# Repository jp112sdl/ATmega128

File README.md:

# ATmega128

```
orig. Fuse:
(E:FF, H:09, L:3F)
```

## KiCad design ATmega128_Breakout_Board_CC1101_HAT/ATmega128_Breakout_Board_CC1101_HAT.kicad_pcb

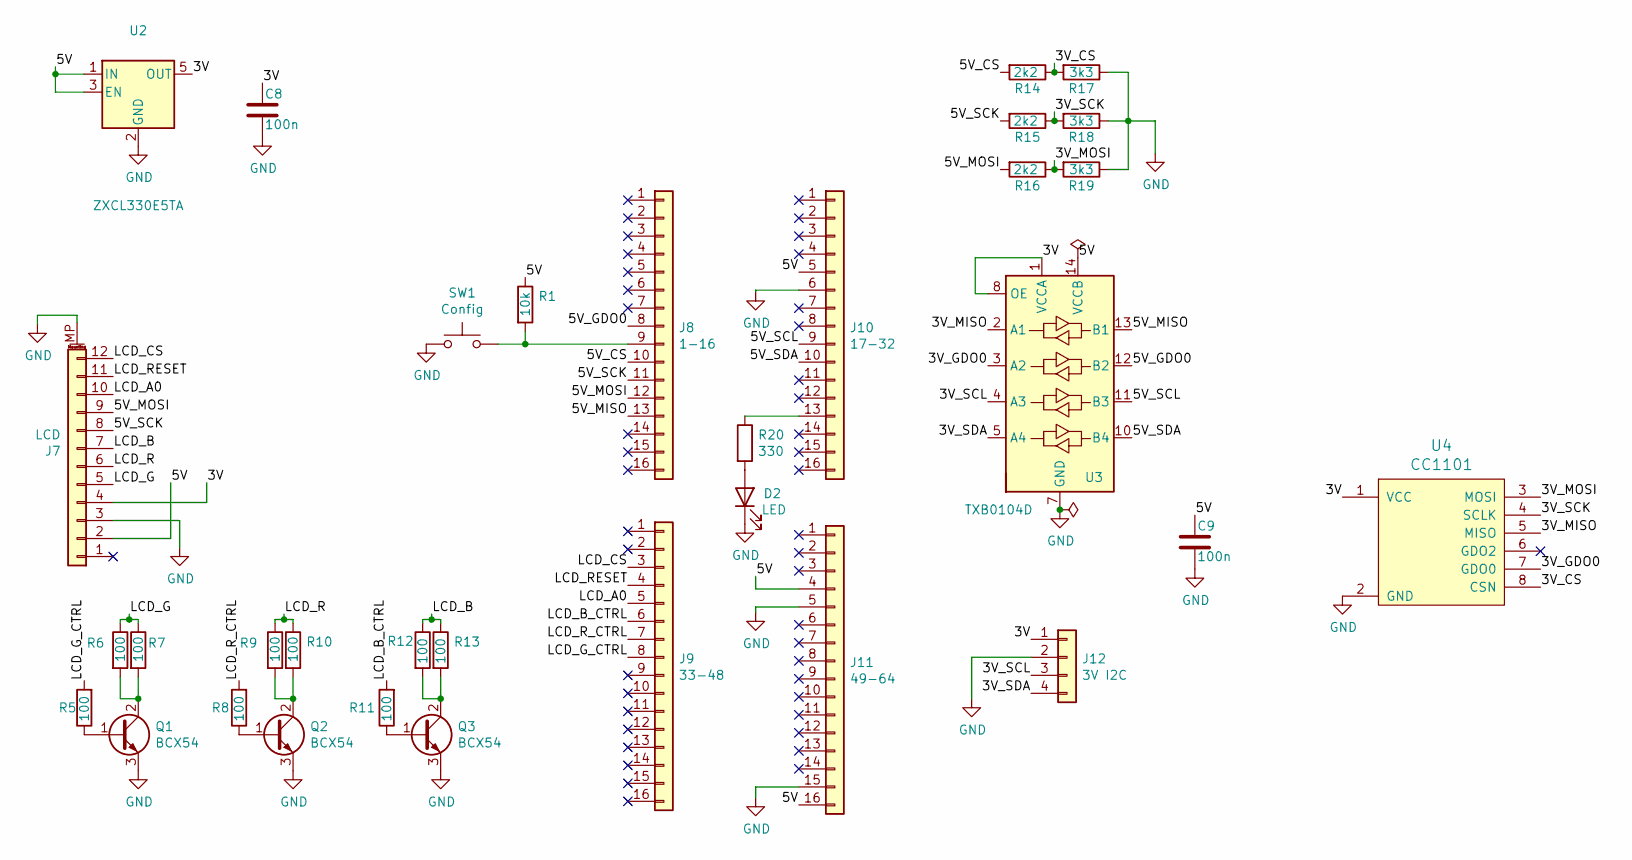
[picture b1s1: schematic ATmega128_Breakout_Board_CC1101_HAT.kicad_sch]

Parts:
C8, C9: 100n; C_0805_2012Metric_Pad1.15x1.40mm_HandSolder
D2: LED; LED_0805_2012Metric_Pad1.15x1.40mm_HandSolder
J7: LCD; TE_1-84953-2_1x12-1MP_P1.0mm_Horizontal
J8: 1-16; PinHeader_1x16_P2.54mm_Vertical
J9: 33-48; PinHeader_1x16_P2.54mm_Vertical
J10: 17-32; PinHeader_1x16_P2.54mm_Vertical
J11: 49-64; PinHeader_1x16_P2.54mm_Vertical
J12: 3V I2C; PinHeader_1x04_P2.54mm_Vertical
Q1, Q2, Q3: BCX54; SOT-89-3
R1: 10k; R_0805_2012Metric_Pad1.15x1.40mm_HandSolder
R5, R6, R7, R8, R9, R10, R11, R12, R13: 100; R_0805_2012Metric_Pad1.15x1.40mm_HandSolder
R14, R15, R16: 2k2; R_0805_2012Metric_Pad1.15x1.40mm_HandSolder
R17, R18, R19: 3k3; R_0805_2012Metric_Pad1.15x1.40mm_HandSolder
R20: 330; R_0805_2012Metric_Pad1.15x1.40mm_HandSolder
SW1: Config; SW_PUSH_6mm_H4.3mm
U2: ZXCL330E5TA; SOT-23-5
U3: TXB0104D; TSSOP-14_4.4x5mm_P0.65mm
U4: CC1101; CC1101_Pads

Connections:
/3V: C8.1, J7.4, J12.1, U2.5 (OUT), U3.1 (VCCA), U3.8 (OE), U4.1 (VCC)
/3V_CS: R14.1, R17.2, U4.8 (CSN)
/3V_GDO0: U3.3 (A2), U4.7 (GDO0)
/3V_MISO: U3.2 (A1), U4.5 (MISO)
/3V_MOSI: R16.1, R19.2, U4.3 (MOSI)
/3V_SCK: R15.1, R18.2, U4.4 (SCLK)
/3V_SCL: J12.3, U3.4 (A3)
/3V_SDA: J12.4, U3.5 (A4)
/5V: C9.1, J7.2, J10.5, J11.4, J11.16, R1.1, U2.1 (IN), U2.3 (EN), U3.14 (VCCB)
/5V_CS: J8.10, R14.2
/5V_GDO0: J8.8, U3.12 (B2)
/5V_MISO: J8.13, U3.13 (B1)
/5V_MOSI: J7.9, J8.12, R16.2
/5V_SCK: J7.8, J8.11, R15.2
/5V_SCL: J10.9, U3.11 (B3)
/5V_SDA: J10.10, U3.10 (B4)
/LCD_A0: J7.10, J9.5
/LCD_B: J7.7, R12.1, R13.1
/LCD_B_CTRL: J9.6, R11.2
/LCD_CS: J7.12, J9.3
/LCD_G: J7.5, R6.1, R7.1
/LCD_G_CTRL: J9.8, R5.2
/LCD_R: J7.6, R9.1, R10.1
/LCD_RESET: J7.11, J9.4
/LCD_R_CTRL: J9.7, R8.2
GND: C8.2, C9.2, D2.1 (K), J7.3, J7.MP (MountPin), J10.6, J11.5, J11.15, J12.2, Q1.3 (E), Q2.3 (E), Q3.3 (E), R17.1, R18.1, R19.1, SW1.1, U2.2 (GND), U3.7 (GND), U4.2 (GND)
unnamed: D2.2 (A), R20.2
unnamed: J8.9, R1.2, SW1.2
unnamed: J10.13, R20.1
unnamed: Q1.1 (B), R5.1
unnamed: Q1.2 (C), R6.2, R7.2
unnamed: Q2.1 (B), R8.1
unnamed: Q2.2 (C), R9.2, R10.2
unnamed: Q3.1 (B), R11.1
unnamed: Q3.2 (C), R12.2, R13.2

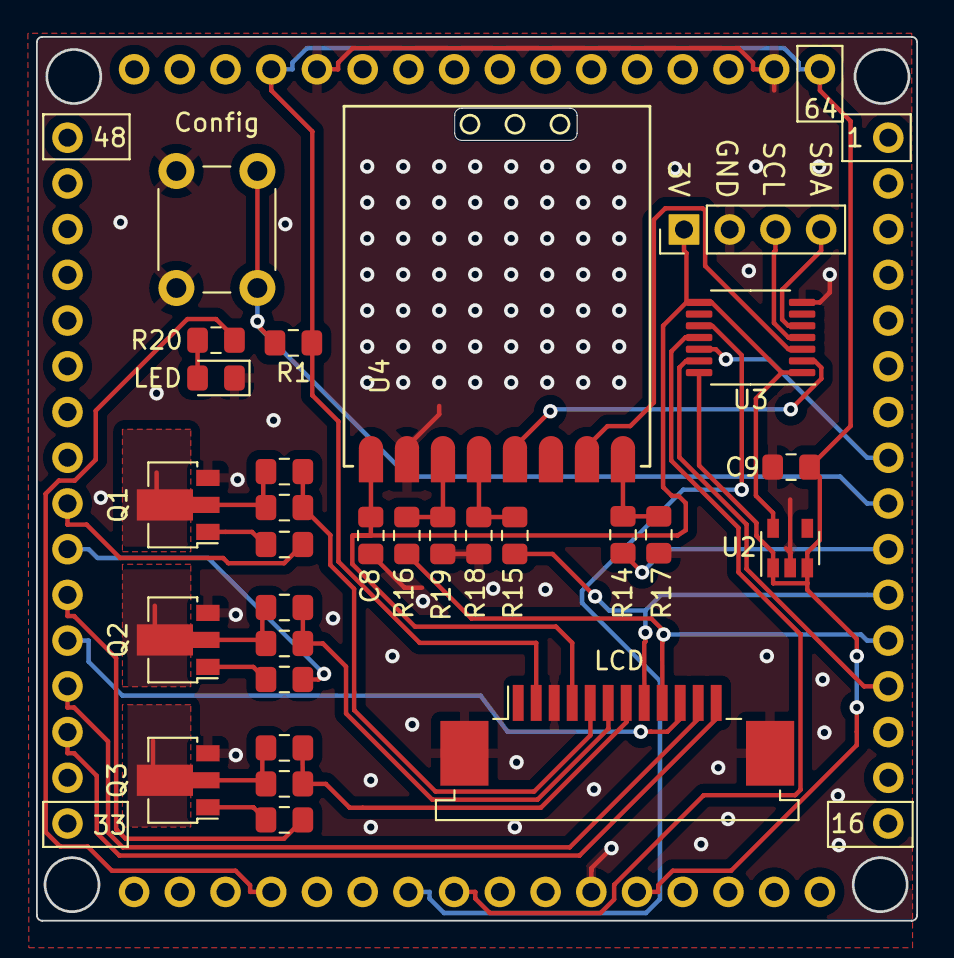
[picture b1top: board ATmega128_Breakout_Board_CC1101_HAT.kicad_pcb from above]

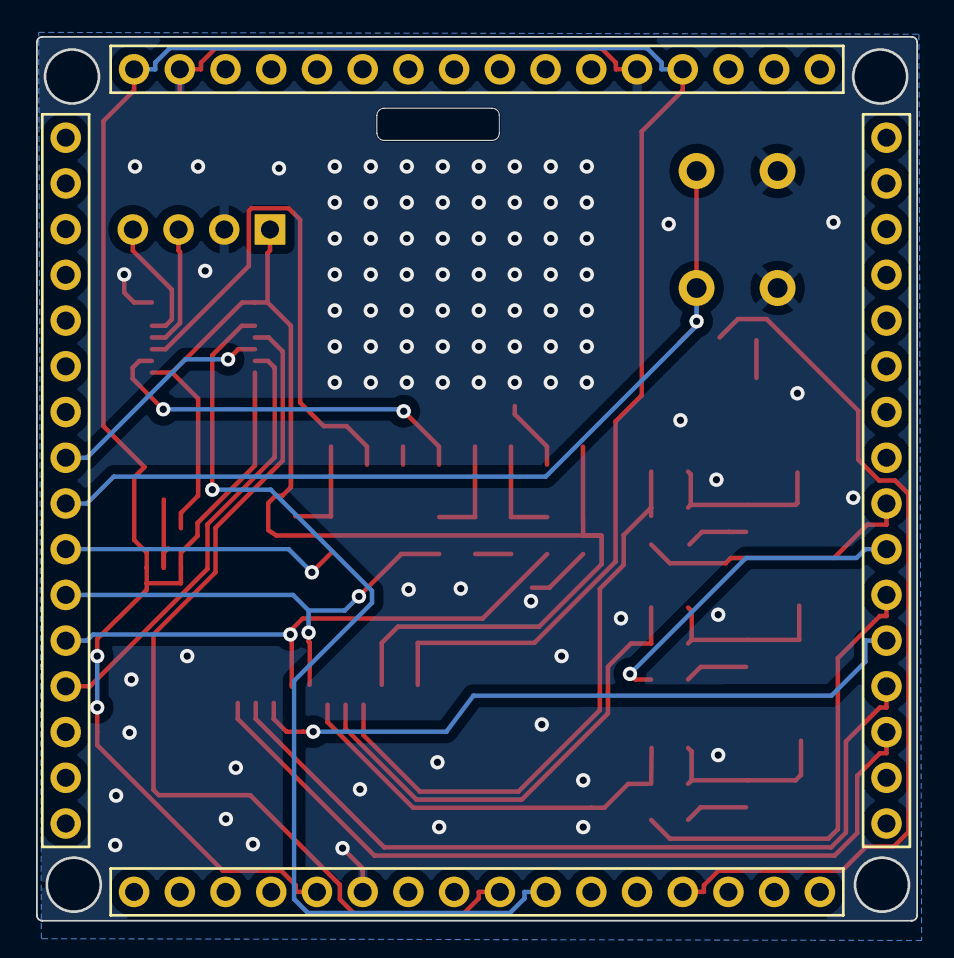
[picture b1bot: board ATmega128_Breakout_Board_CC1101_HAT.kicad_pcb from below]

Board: 2 copper layers, 48.9 x 49.1 mm, 33 parts (4 on the bottom side), 35 nets.

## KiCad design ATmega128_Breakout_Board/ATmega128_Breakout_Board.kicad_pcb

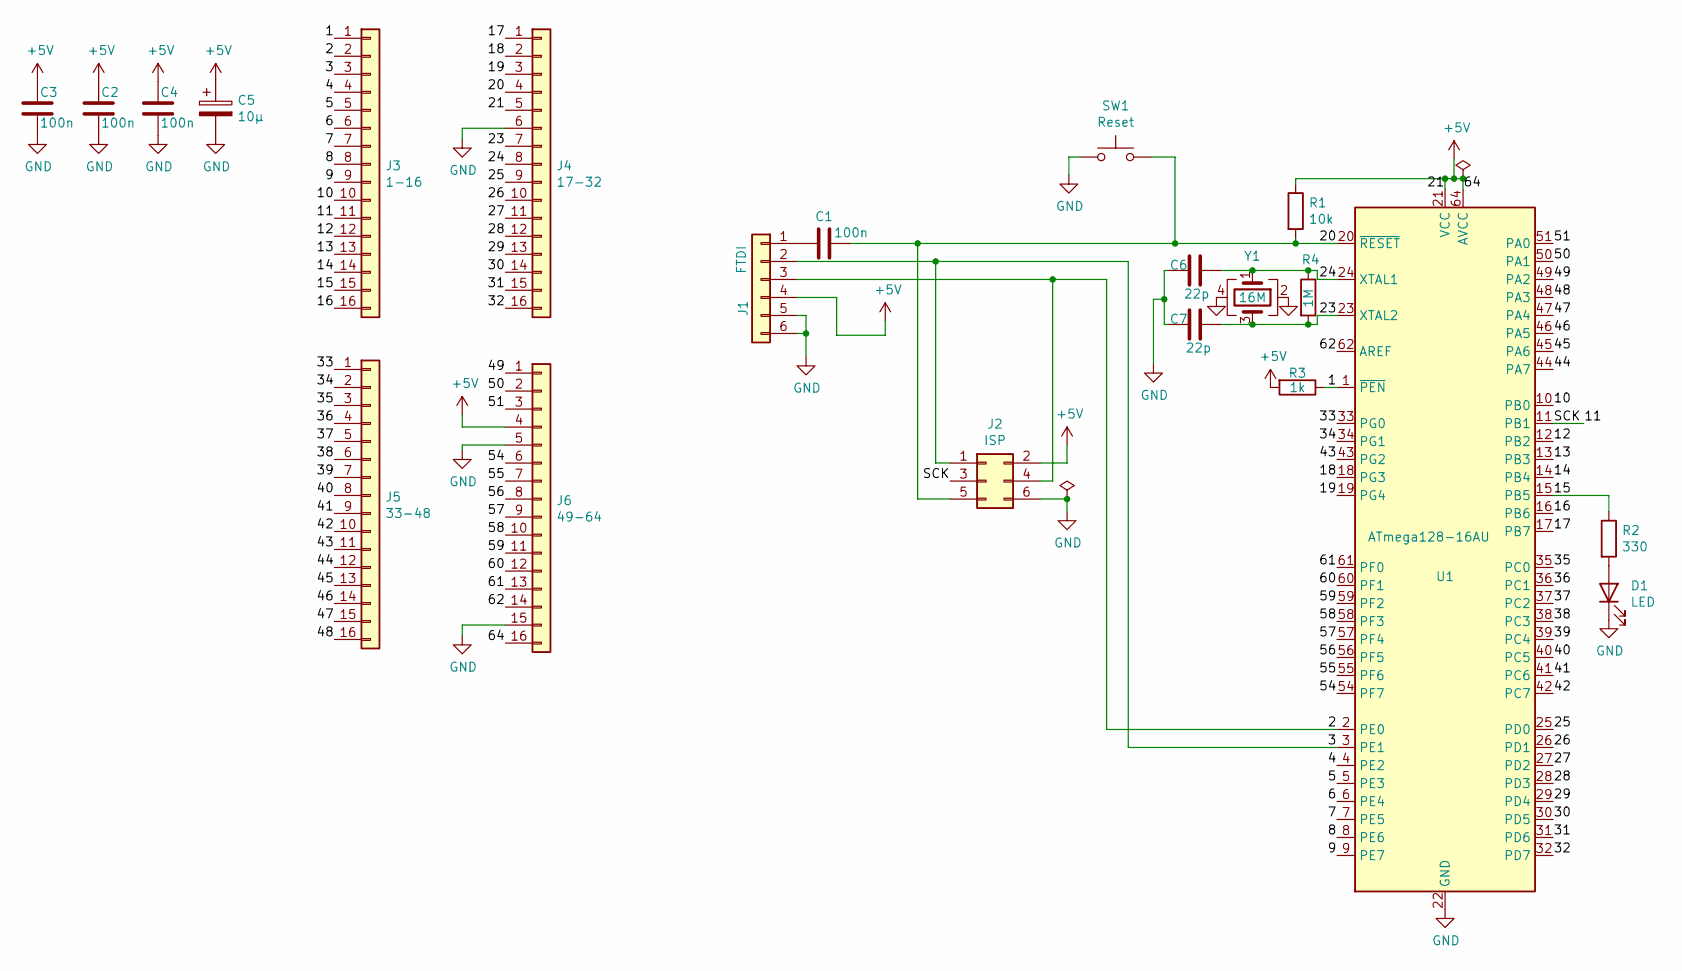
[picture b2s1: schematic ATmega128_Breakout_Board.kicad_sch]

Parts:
C1, C2, C3, C4: 100n; C_0805_2012Metric_Pad1.15x1.40mm_HandSolder
C5: 10µ; CP_EIA-3528-12_Kemet-T_Pad1.50x2.35mm_HandSolder
C6, C7: 22p; C_0805_2012Metric_Pad1.15x1.40mm_HandSolder
D1: LED; LED_0805_2012Metric_Pad1.15x1.40mm_HandSolder
J1: FTDI; PinHeader_1x06_P2.54mm_Vertical
J2: ISP; PinHeader_2x03_P2.54mm_Vertical
J3: 1-16; PinHeader_1x16_P2.54mm_Vertical
J4: 17-32; PinHeader_1x16_P2.54mm_Vertical
J5: 33-48; PinHeader_1x16_P2.54mm_Vertical
J6: 49-64; PinHeader_1x16_P2.54mm_Vertical
R1: 10k; R_0805_2012Metric_Pad1.15x1.40mm_HandSolder
R2: 330; R_0805_2012Metric_Pad1.15x1.40mm_HandSolder
R3: 1k; R_0805_2012Metric_Pad1.15x1.40mm_HandSolder
R4: 1M; R_0805_2012Metric_Pad1.15x1.40mm_HandSolder
SW1: Reset; SW_PUSH_6mm_H5mm
U1: ATmega128-16AU; TQFP-64_14x14mm_P0.8mm
Y1: 16M; Crystal_SMD_EuroQuartz_MQ-4Pin_7.0x5.0mm_HandSoldering

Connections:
+5V: C2.1, C3.1, C4.1, C5.1, J1.4, J2.2, J4.5, J6.4, J6.16, R1.1, R3.2, U1.21 (VCC), U1.52 (VCC), U1.64 (AVCC)
/1: J3.1, R3.1, U1.1 (~PEN)
/2: J1.3, J2.4, J3.2, U1.2 (PE0)
/3: J1.2, J2.1, J3.3, U1.3 (PE1)
/4: J3.4, U1.4 (PE2)
/5: J3.5, U1.5 (PE3)
/6: J3.6, U1.6 (PE4)
/7: J3.7, U1.7 (PE5)
/8: J3.8, U1.8 (PE6)
/9: J3.9, U1.9 (PE7)
/10: J3.10, U1.10 (PB0)
/11: J2.3, J3.11, U1.11 (PB1)
/12: J3.12, U1.12 (PB2)
/13: J3.13, U1.13 (PB3)
/14: J3.14, U1.14 (PB4)
/15: J3.15, R2.1, U1.15 (PB5)
/16: J3.16, U1.16 (PB6)
/17: J4.1, U1.17 (PB7)
/18: J4.2, U1.18 (PG3)
/19: J4.3, U1.19 (PG4)
/20: C1.1, J2.5, J4.4, R1.2, SW1.2, U1.20 (~RESET)
/23: C7.2, J4.7, R4.2, U1.23 (XTAL2), Y1.3
/24: C6.2, J4.8, R4.1, U1.24 (XTAL1), Y1.1
/25: J4.9, U1.25 (PD0)
/26: J4.10, U1.26 (PD1)
/27: J4.11, U1.27 (PD2)
/28: J4.12, U1.28 (PD3)
/29: J4.13, U1.29 (PD4)
/30: J4.14, U1.30 (PD5)
/31: J4.15, U1.31 (PD6)
/32: J4.16, U1.32 (PD7)
/33: J5.1, U1.33 (PG0)
/34: J5.2, U1.34 (PG1)
/35: J5.3, U1.35 (PC0)
/36: J5.4, U1.36 (PC1)
/37: J5.5, U1.37 (PC2)
/38: J5.6, U1.38 (PC3)
/39: J5.7, U1.39 (PC4)
/40: J5.8, U1.40 (PC5)
/41: J5.9, U1.41 (PC6)
/42: J5.10, U1.42 (PC7)
/43: J5.11, U1.43 (PG2)
/44: J5.12, U1.44 (PA7)
/45: J5.13, U1.45 (PA6)
/46: J5.14, U1.46 (PA5)
/47: J5.15, U1.47 (PA4)
/48: J5.16, U1.48 (PA3)
/49: J6.1, U1.49 (PA2)
/50: J6.2, U1.50 (PA1)
/51: J6.3, U1.51 (PA0)
/54: J6.6, U1.54 (PF7)
/55: J6.7, U1.55 (PF6)
/56: J6.8, U1.56 (PF5)
/57: J6.9, U1.57 (PF4)
/58: J6.10, U1.58 (PF3)
/59: J6.11, U1.59 (PF2)
/60: J6.12, U1.60 (PF1)
/61: J6.13, U1.61 (PF0)
/62: J6.14, U1.62 (AREF)
GND: C2.2, C3.2, C4.2, C5.2, C6.1, C7.1, D1.1 (K), J1.5, J1.6, J2.6, J4.6, J6.5, J6.15, SW1.1, U1.22 (GND), U1.53 (GND), U1.63 (GND), Y1.2, Y1.4
unnamed: C1.2, J1.1
unnamed: D1.2 (A), R2.2

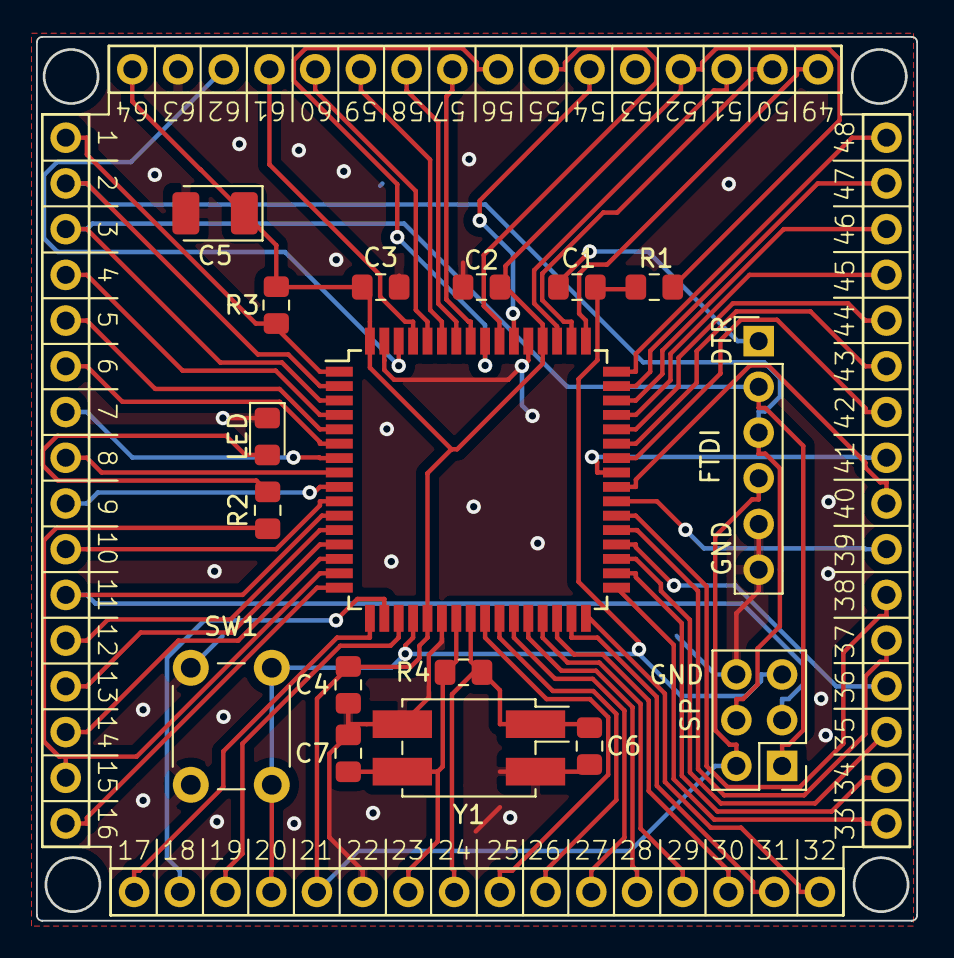
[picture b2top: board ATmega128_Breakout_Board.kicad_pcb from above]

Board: 2 copper layers, 48.9 x 49.1 mm, 21 parts (0 on the bottom side), 62 nets.

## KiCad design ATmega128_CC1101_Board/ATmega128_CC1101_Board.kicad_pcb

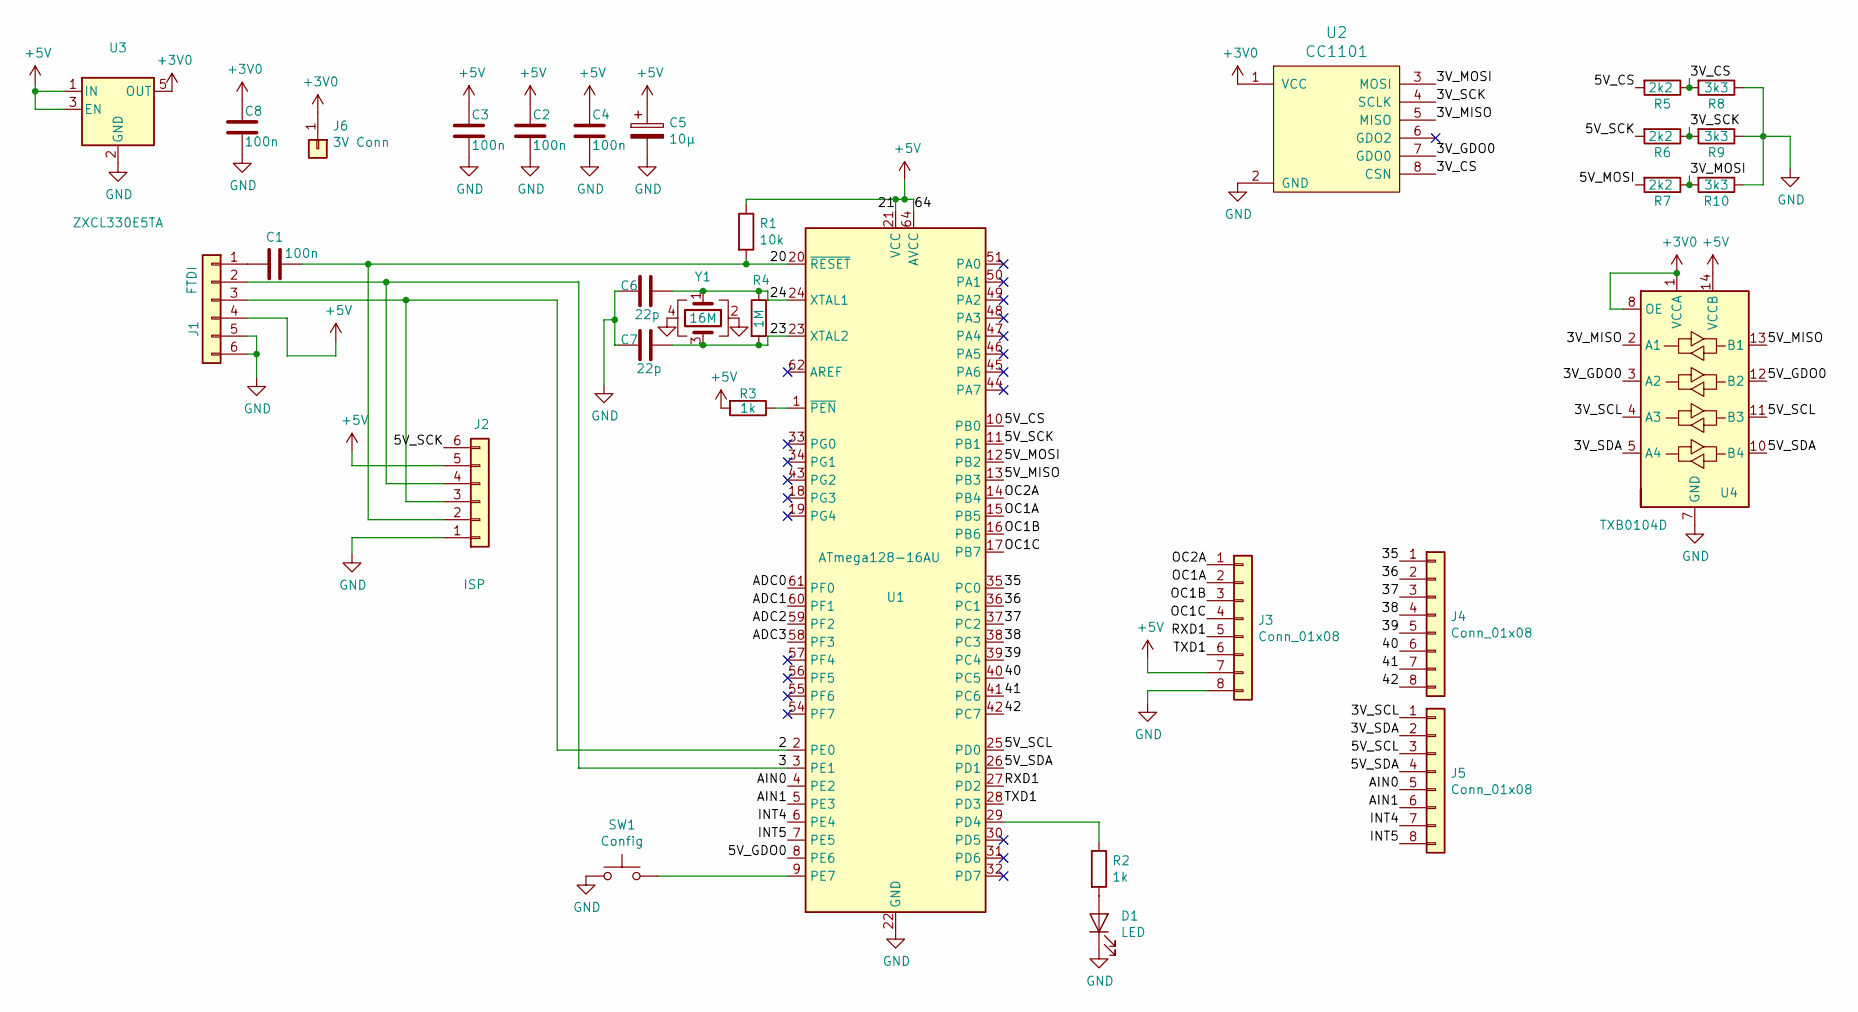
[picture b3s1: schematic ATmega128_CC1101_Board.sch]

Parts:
C1, C2, C3, C4, C8: 100n; C_0805_2012Metric_Pad1.15x1.40mm_HandSolder
C5: 10µ; CP_EIA-3528-12_Kemet-T_Pad1.50x2.35mm_HandSolder
C6, C7: 22p; C_0805_2012Metric_Pad1.15x1.40mm_HandSolder
D1: LED; LED_0805_2012Metric_Pad1.15x1.40mm_HandSolder
J1: FTDI; PinHeader_1x06_P2.54mm_Vertical
J2: ISP; PinPads_ISP
J3, J4, J5: Conn_01x08; PinHeader_1x08_P2.54mm_Vertical
J6: 3V Conn; PinHeader_1x01_P2.54mm_Vertical
R1: 10k; R_0805_2012Metric_Pad1.15x1.40mm_HandSolder
R2, R3: 1k; R_0805_2012Metric_Pad1.15x1.40mm_HandSolder
R4: 1M; R_0805_2012Metric_Pad1.15x1.40mm_HandSolder
R5, R6, R7: 2k2; R_0805_2012Metric_Pad1.15x1.40mm_HandSolder
R8, R9, R10: 3k3; R_0805_2012Metric_Pad1.15x1.40mm_HandSolder
SW1: Config; SW_SPST_PTS645
U1: ATmega128-16AU; TQFP-64_14x14mm_P0.8mm
U2: CC1101; CC1101_Pads
U3: ZXCL330E5TA; SOT-23-5
U4: TXB0104D; TSSOP-14_4.4x5mm_P0.65mm
Y1: 16M; Crystal_SMD_EuroQuartz_MQ-4Pin_7.0x5.0mm_HandSoldering

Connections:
+3V0: C8.1, J6.1, U2.1 (VCC), U3.5 (OUT), U4.1 (VCCA), U4.8 (OE)
+5V: C2.1, C3.1, C4.1, C5.1, J1.4, J2.5, J3.7, R1.1, R3.2, U1.21 (VCC), U1.52 (VCC), U1.64 (AVCC), U3.1 (IN), U3.3 (EN), U4.14 (VCCB)
/2: J1.3, J2.3, U1.2 (PE0)
/3: J1.2, J2.4, U1.3 (PE1)
/3V_CS: R5.1, R8.2, U2.8 (CSN)
/3V_GDO0: U2.7 (GDO0), U4.3 (A2)
/3V_MISO: U2.5 (MISO), U4.2 (A1)
/3V_MOSI: R7.1, R10.2, U2.3 (MOSI)
/3V_SCK: R6.1, R9.2, U2.4 (SCLK)
/3V_SCL: J5.1, U4.4 (A3)
/3V_SDA: J5.2, U4.5 (A4)
/5V_CS: R5.2, U1.10 (PB0)
/5V_GDO0: U1.8 (PE6), U4.12 (B2)
/5V_MISO: U1.13 (PB3), U4.13 (B1)
/5V_MOSI: R7.2, U1.12 (PB2)
/5V_SCK: J2.6, R6.2, U1.11 (PB1)
/5V_SCL: J5.3, U1.25 (PD0), U4.11 (B3)
/5V_SDA: J5.4, U1.26 (PD1), U4.10 (B4)
/20: C1.1, J2.2, R1.2, U1.20 (~RESET)
/23: C7.2, R4.2, U1.23 (XTAL2), Y1.3
/24: C6.2, R4.1, U1.24 (XTAL1), Y1.1
/35: J4.1, U1.35 (PC0)
/36: J4.2, U1.36 (PC1)
/37: J4.3, U1.37 (PC2)
/38: J4.4, U1.38 (PC3)
/39: J4.5, U1.39 (PC4)
/40: J4.6, U1.40 (PC5)
/41: J4.7, U1.41 (PC6)
/42: J4.8, U1.42 (PC7)
/ADC0: U1.61 (PF0)
/ADC1: U1.60 (PF1)
/ADC2: U1.59 (PF2)
/ADC3: U1.58 (PF3)
/AIN0: J5.5, U1.4 (PE2)
/AIN1: J5.6, U1.5 (PE3)
/INT4: J5.7, U1.6 (PE4)
/INT5: J5.8, U1.7 (PE5)
/OC1A: J3.2, U1.15 (PB5)
/OC1B: J3.3, U1.16 (PB6)
/OC1C: J3.4, U1.17 (PB7)
/OC2A: J3.1, U1.14 (PB4)
/RXD1: J3.5, U1.27 (PD2)
/TXD1: J3.6, U1.28 (PD3)
GND: C2.2, C3.2, C4.2, C5.2, C6.1, C7.1, C8.2, D1.1 (K), J1.5, J1.6, J2.1, J3.8, R8.1, R9.1, R10.1, SW1.1, U1.22 (GND), U1.53 (GND), U1.63 (GND), U2.2 (GND), U3.2 (GND), U4.7 (GND), Y1.2, Y1.4
unnamed: C1.2, J1.1
unnamed: D1.2 (A), R2.2
unnamed: R2.1, U1.29 (PD4)
unnamed: R3.1, U1.1 (~PEN)
unnamed: SW1.2, U1.9 (PE7)

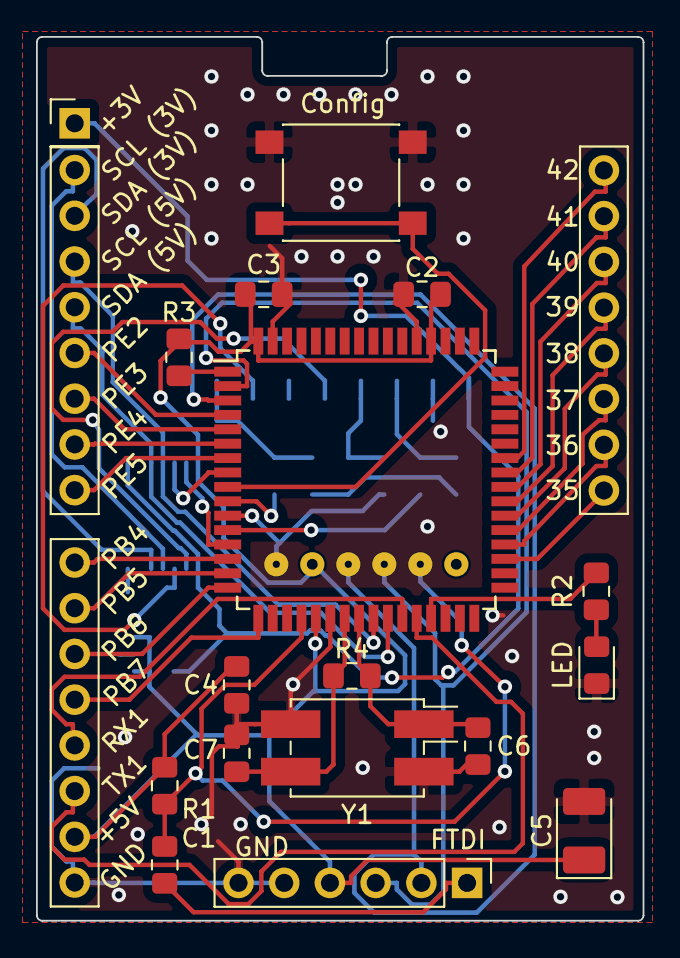
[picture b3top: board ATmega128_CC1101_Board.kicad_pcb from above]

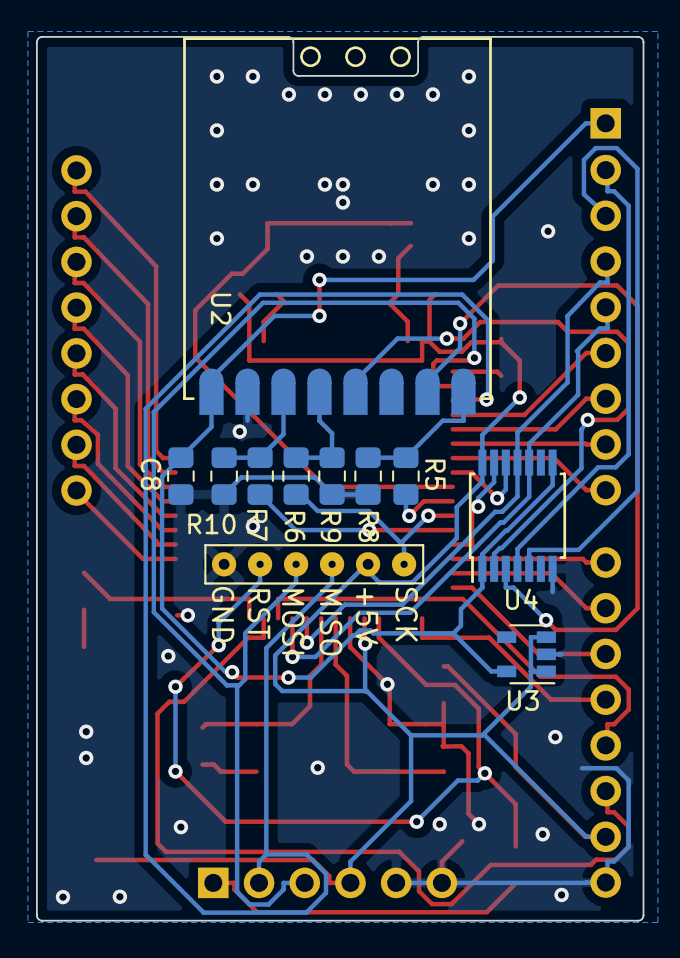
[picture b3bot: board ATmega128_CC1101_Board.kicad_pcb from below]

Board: 2 copper layers, 33.7 x 49.1 mm, 31 parts (11 on the bottom side), 45 nets.

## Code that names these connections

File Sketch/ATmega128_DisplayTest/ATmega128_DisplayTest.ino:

#define LCD_CS     28
#define LCD_RST    29
#define LCD_DC     30
#define LCD_BLUE   31
#define LCD_RED    32
#define LCD_GREEN  33

#define HAT_LED    22 //PD4
#define HAT_BTN     7 //PE7 INT7

#define CC1101_CS   8 //PB0
#define CC1101_GDO0 6 //PE6 INT6

#define PEERS_PER_CHANNEL 6
#define MSG_INTERVAL        10
#define CONFIG_BUTTON_PIN HAT_BTN

#include <U8g2lib.h>
#include <SPI.h>

#include "TM12864_LCD.h"
#include <AskSinPP.h>
#include <MultiChannelDevice.h>
#ifndef ASKSIN_PLUS_PLUS_VERSION_STR
  #define ASKSIN_PLUS_PLUS_VERSION_STR ASKSIN_PLUS_PLUS_VERSION
#endif
U8G2_ST7565_64128N_F_4W_HW_SPI display(U8G2_R0, LCD_CS, LCD_DC, LCD_RST);
TM12864<LCD_RED, LCD_GREEN, LCD_BLUE> tm12864(display);

using namespace as;

// define all device properties
const struct DeviceInfo PROGMEM devinfo = {
  {0x34, 0x56, 0xa6},     // Device ID
  "JPTH10I999",           // Device Serial
  {0x00, 0x3f},           // Device Model Indoor
  0x10,                   // Firmware Version
  as::DeviceType::THSensor, // Device Type
  {0x01, 0x00}            // Info Bytes
};

typedef LibSPI<CC1101_CS> SPIType;
typedef Radio<SPIType, CC1101_GDO0> RadioType;
typedef StatusLed<HAT_LED> LedType;
typedef AskSin<LedType, NoBattery, RadioType> Hal;
Hal hal;

class WeatherEventMsg : public Message {
  public:
    void init(uint8_t msgcnt, int16_t temp, uint8_t humidity, bool batlow) {
      uint8_t t1 = (temp >> 8) & 0x7f;
      uint8_t t2 = temp & 0xff;
      if ( batlow == true ) {
        t1 |= 0x80; // set bat low bit
      }
      Message::init(0xc, msgcnt, 0x70, BIDI | WKMEUP, t1, t2);
      pload[0] = humidity;
    }
};

class WeatherChannel : public Channel<Hal, List1, EmptyList, List4, PEERS_PER_CHANNEL, List0>, public Alarm {
    WeatherEventMsg msg;
    int16_t         temp;
    uint8_t         humidity;
  public:
    WeatherChannel () : Channel(), Alarm(2), temp(0), humidity(0) {}
    virtual ~WeatherChannel () {}

    virtual void trigger (__attribute__ ((unused)) AlarmClock& clock) {
      tick = seconds2ticks(MSG_INTERVAL);
      clock.add(*this);

      temp = 245;
      humidity = 56;

      msg.init(device().nextcount(), temp, humidity, false);
      device().broadcastEvent(msg);
    }

    void setup(Device<Hal, List0>* dev, uint8_t number, uint16_t addr) {
      Channel::setup(dev, number, addr);
      sysclock.add(*this);
    }

    uint8_t status () const { return 0; }
    uint8_t flags () const { return 0; }
};

typedef MultiChannelDevice<Hal, WeatherChannel, 1> WeatherType;
WeatherType sdev(devinfo, 0x20);
ConfigButton<WeatherType> cfgBtn(sdev);

void setup(void) {

  DINIT(57600, ASKSIN_PLUS_PLUS_IDENTIFIER);

  tm12864.initLCD();
  tm12864.setALL(LED_OFF);

  tm12864.setGREEN(LED_ON);


  const char * title        PROGMEM = "ATmega128";
  const char * asksinpp     PROGMEM = "AskSin++";
  const char * version      PROGMEM = "V " ASKSIN_PLUS_PLUS_VERSION_STR;
  const char * compiledMsg  PROGMEM = "compiled on";
  const char * compiledDate PROGMEM = __DATE__ " " __TIME__;

  display.setFont(u8g2_font_helvB08_tr);
  display.setCursor(tm12864.centerPosition(title), 10);
  display.print(title);

  display.setFont(u8g2_font_helvR08_tr);
  display.setCursor(tm12864.centerPosition(asksinpp), 26);
  display.print(asksinpp);
  display.setCursor(tm12864.centerPosition(version), 38);
  display.print(version);

  display.setFont(u8g2_font_profont10_mf);
  display.setCursor(tm12864.centerPosition(compiledMsg), 54);
  display.print(compiledMsg);
  display.setCursor(tm12864.centerPosition(compiledDate), 64);
  display.print(compiledDate);
  display.sendBuffer();

  sdev.init(hal);
  buttonISR(cfgBtn, CONFIG_BUTTON_PIN);
  sdev.initDone();
}

void loop(void) {
  bool worked = hal.runready();
  bool poll = sdev.pollRadio();
  if ( worked == false && poll == false ) {
    //hal.activity.savePower<Sleep<>>(hal);
  }

}

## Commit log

2020-11-25 formatting
2020-11-25 add freqtest
2021-02-16 fix version string
2024-06-01 board update for new kicad version
